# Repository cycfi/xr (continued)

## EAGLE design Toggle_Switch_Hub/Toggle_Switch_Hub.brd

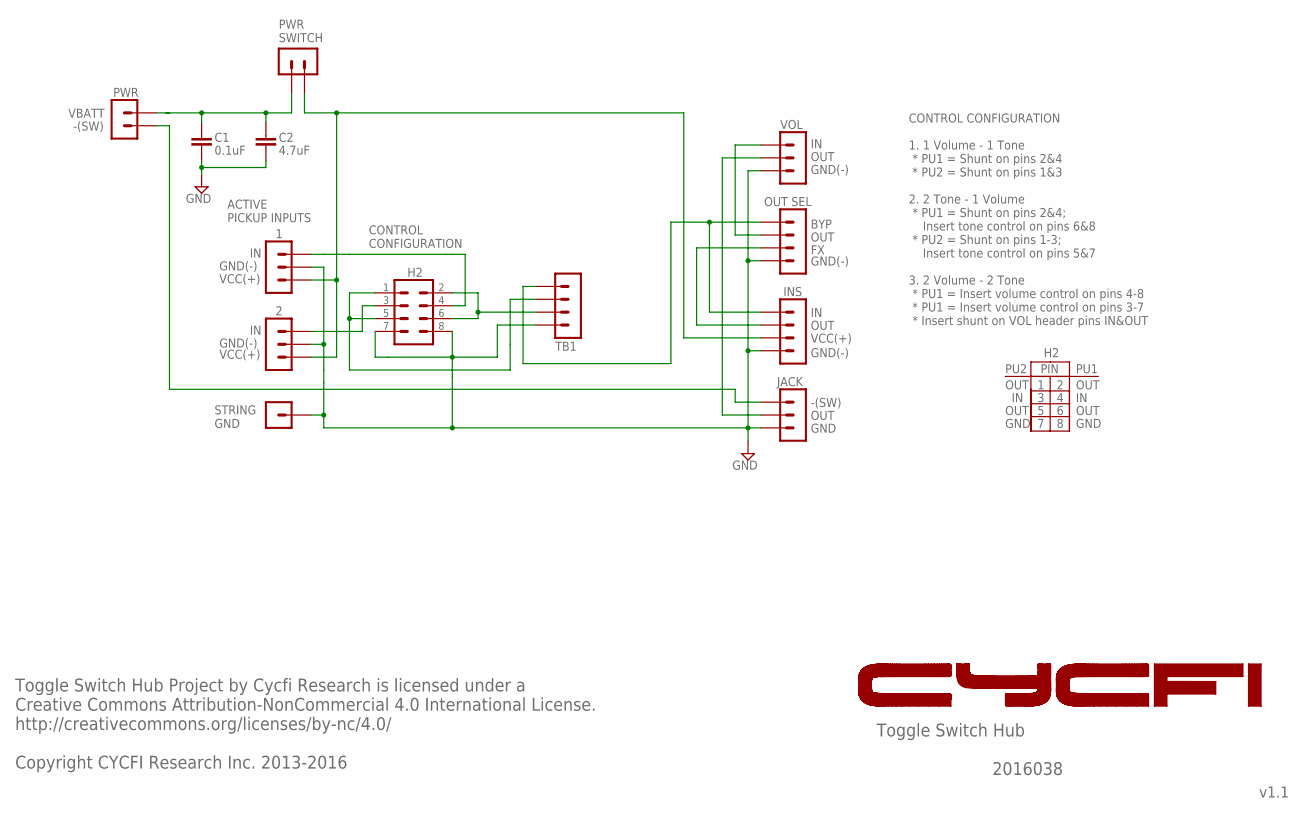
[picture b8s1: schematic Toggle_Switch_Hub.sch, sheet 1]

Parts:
C1: 0.1uF; C0603
C2: 4.7uF; C0603
H2: MA04-2
TB1: 282837-4_TERMINAL_BLOCK; TERMINAL_BLOCK_4P_5.08MM

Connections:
BYP: TB1.P$4 (4); also elsewhere on the board
GND: C1.2, C2.2, H2.7, H2.8, TB1.P$1 (1); also elsewhere on the board
unnamed: H2.2, H2.6, TB1.P$2 (2)
unnamed: H2.1, H2.5, TB1.P$3 (3)
PU1: H2.4; also elsewhere on the board
PU2: H2.3; also elsewhere on the board
VCC: C1.1, C2.1; also elsewhere on the board

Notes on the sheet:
GND(-)
VCC(+)
CONTROL CONFIGURATION
BYP
OUT
-(SW)
GND
VOL
INS
JACK
OUT SEL
PWR SWITCH
ACTIVE PICKUP INPUTS
VBATT
TB1
PWR
PU1
PIN
CONTROL CONFIGURATION 1. 1 Volume - 1 Tone * PU1 = Shunt on pins 2&4 * PU2 = Shunt on pins 1&3 2. 2 Tone - 1 Volume * PU1 = Shunt on pins 2&4; Insert tone control on pins 6&8 * PU2 = Shunt on pins 1-3; Insert tone control on pins 5&7 3. 2 Volume - 2 Tone * PU1 = Insert volume control on pins 4-8 * 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
PU2
STRING GND
Toggle Switch Hub
v1.1
Toggle Switch Hub Project by Cycfi Research is licensed under a Creative Commons Attribution-NonCommercial 4.0 International License. http://creativecommons.org/licenses/by-nc/4.0/ Copyright CYCFI Research Inc. 2013-2016
2016038

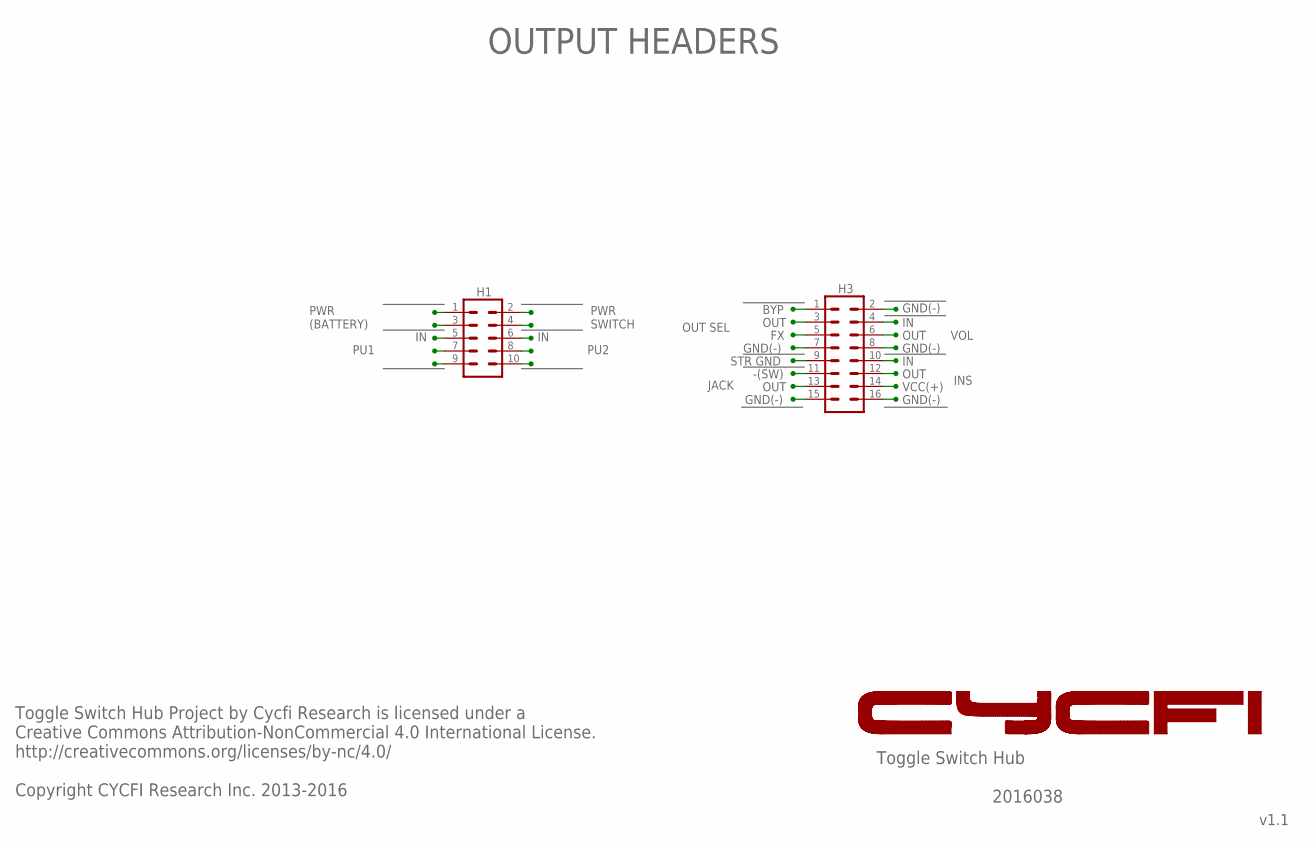
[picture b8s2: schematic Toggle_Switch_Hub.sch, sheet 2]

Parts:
H1: MA05-2
H3: MA08-2

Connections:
BYP: H3.1, H3.10; also elsewhere on the board
FX: H3.5, H3.12
GND: H1.7, H1.8, H3.2, H3.7, H3.8, H3.9, H3.15, H3.16; also elsewhere on the board
OUT: H3.3, H3.4
OUT(VOL): H3.6, H3.13
PU1: H1.5; also elsewhere on the board
PU2: H1.6; also elsewhere on the board
SW: H1.3, H3.11
VCC: H1.1, H1.2; also elsewhere on the board
VIN: H1.4, H1.9, H1.10, H3.14

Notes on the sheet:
GND(-)
OUT
VCC(+)
-(SW)
BYP
STR GND
OUTPUT HEADERS
PWR (BATTERY)
PU1
PU2
PWR SWITCH
OUT SEL
JACK
VOL
INS
Toggle Switch Hub
v1.1
Toggle Switch Hub Project by Cycfi Research is licensed under a Creative Commons Attribution-NonCommercial 4.0 International License. http://creativecommons.org/licenses/by-nc/4.0/ Copyright CYCFI Research Inc. 2013-2016
2016038

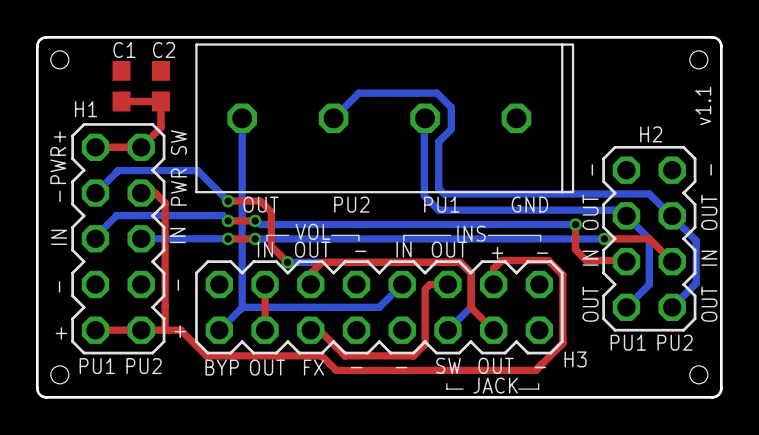
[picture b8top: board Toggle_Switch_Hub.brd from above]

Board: 2 copper layers, 38.0 x 20.0 mm, 6 parts (0 on the bottom side), 12 nets.

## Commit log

2016-02-19 Directory/Files Restructure
2016-02-19 Added Preamp V 1.5
2016-02-23 Updates/ label modifications to make them consistent
2016-10-15 Rename and update drawings
2016-11-07 Revised
2016-12-05 Licenses
2016-12-05 remove caption
2017-02-14 *organize 5-waay switch and its configuration board(a and b) *update license date *remove red frame schem pdf files, change with black frame *update document number
2017-02-14 * correct misspelled word
2017-04-03 Updated schematic licenses
2017-04-03 Updated schematic licenses.
2017-04-04 Updated broken .sch files
2017-06-02 initial commit 5-Way Schematic
2017-09-05 Updated BOM and Document Number
2017-12-20 Cycfi Eagle Libraries
